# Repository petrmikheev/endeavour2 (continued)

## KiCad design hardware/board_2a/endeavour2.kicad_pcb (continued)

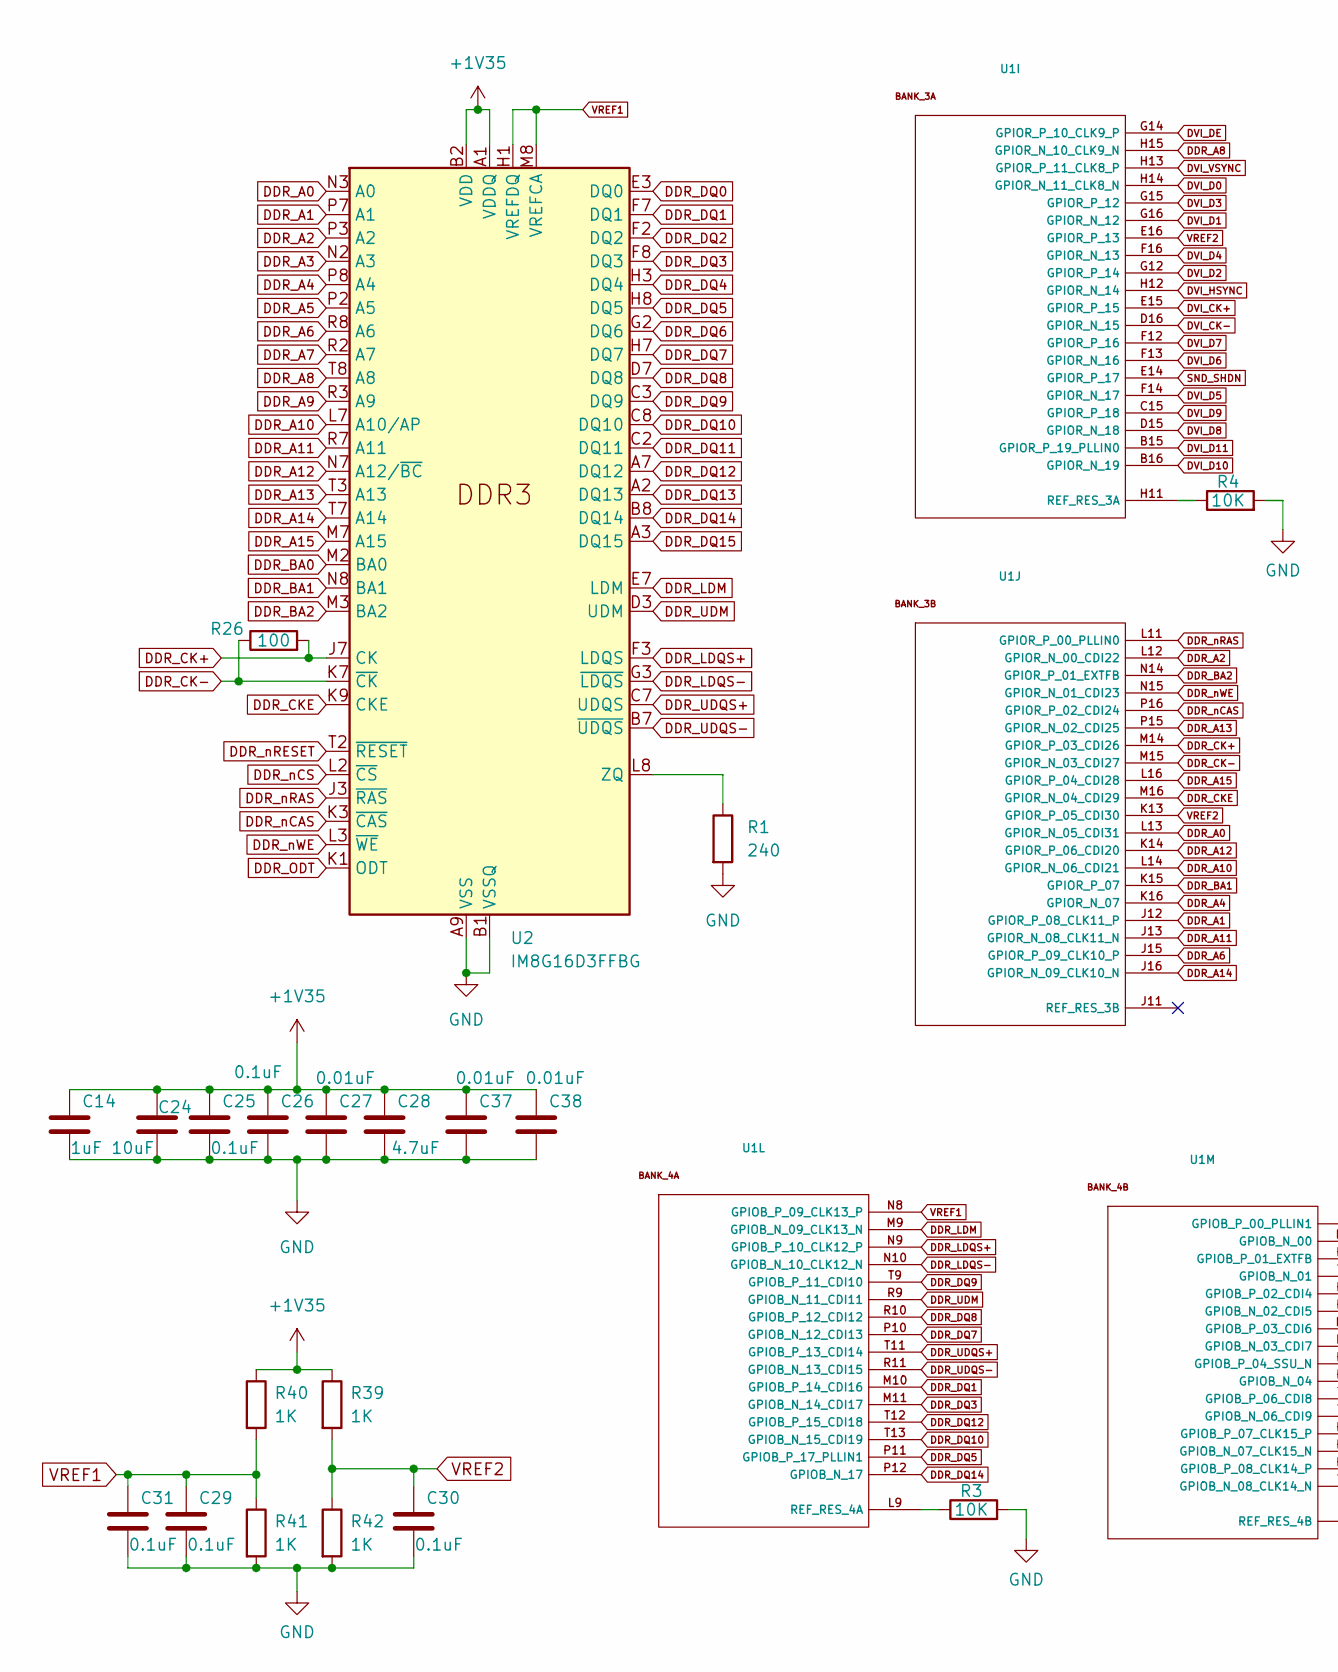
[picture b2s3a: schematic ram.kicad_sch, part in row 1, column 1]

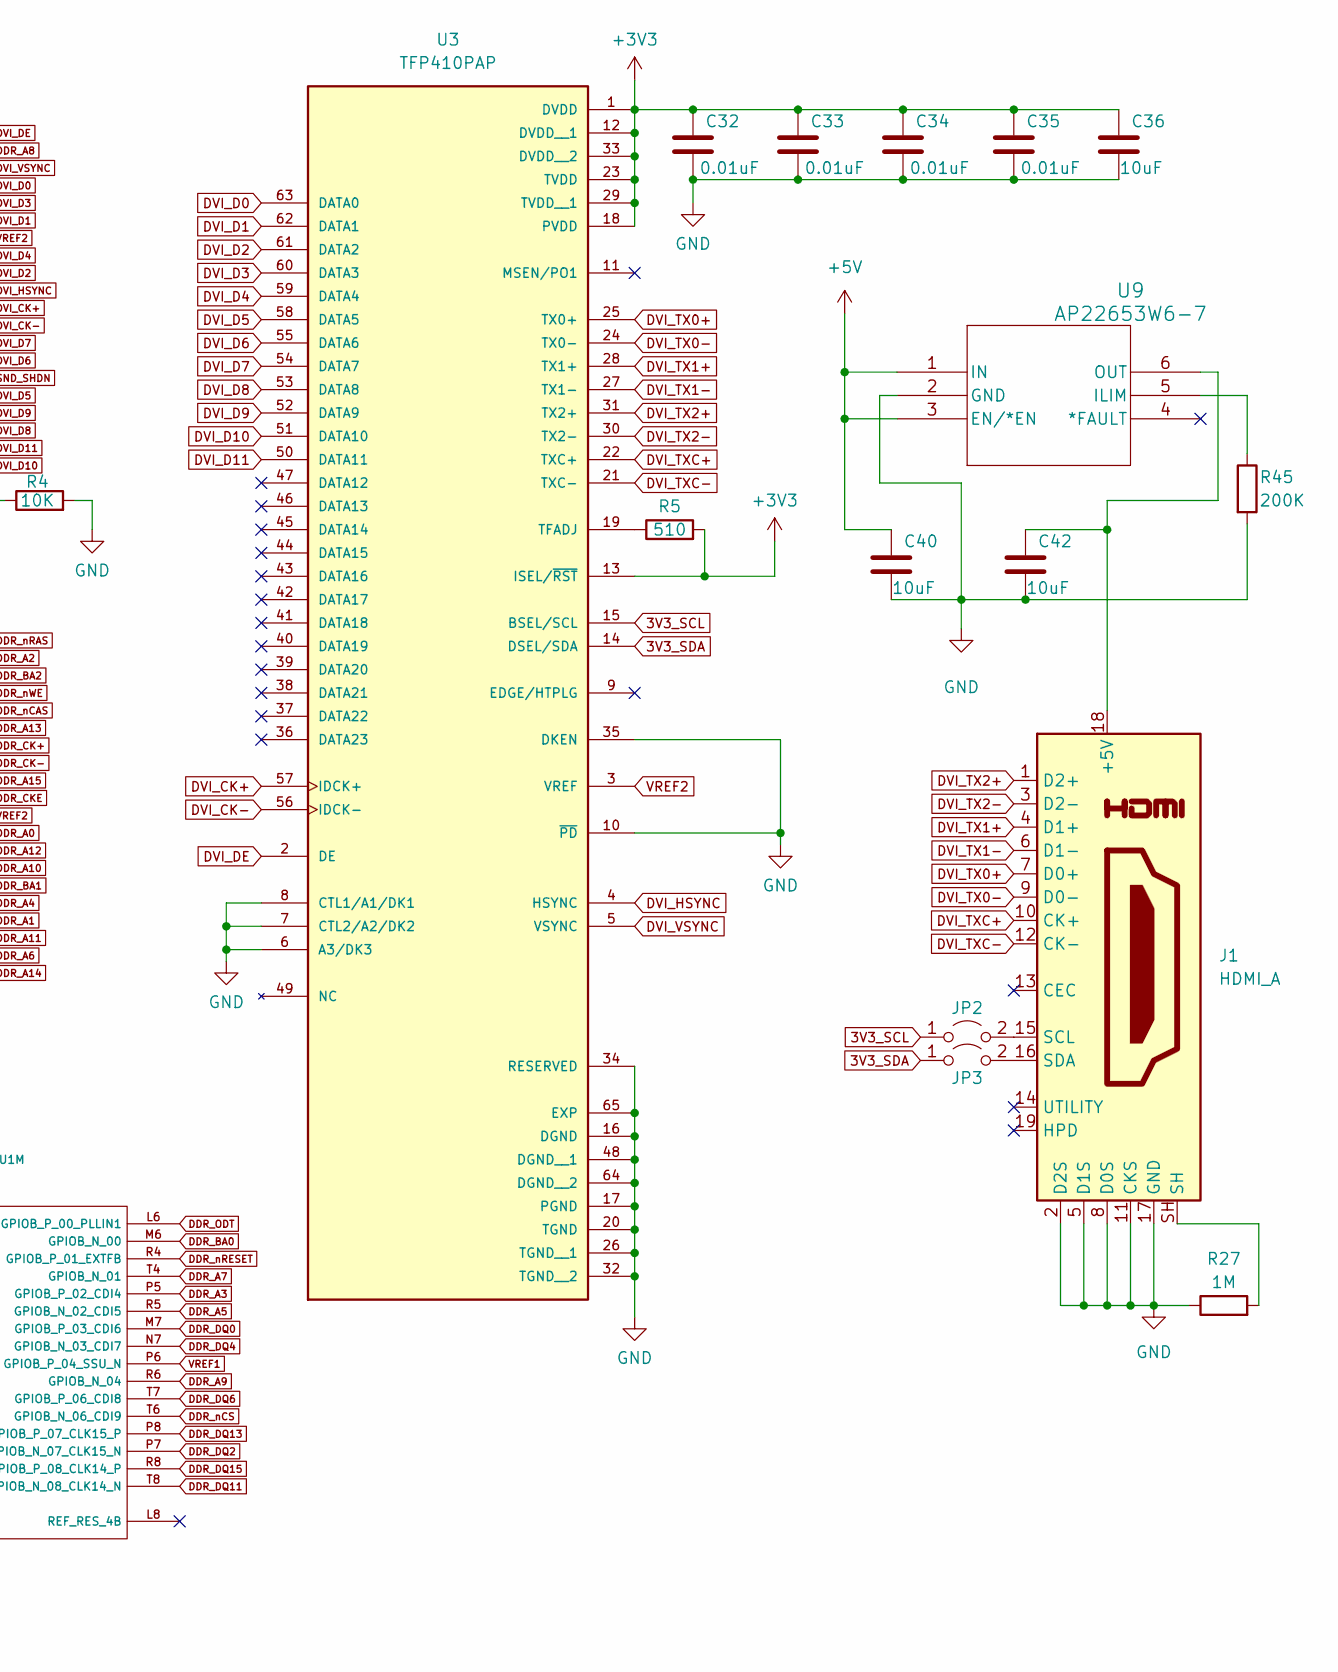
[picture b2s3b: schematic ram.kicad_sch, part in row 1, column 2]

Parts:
C14: 1uF; C_0603_1608Metric
C24, C36, C40, C42: 10uF; C_0603_1608Metric
C25, C26, C29, C30, C31: 0.1uF; C_0603_1608Metric
C27, C32, C33, C34, C35, C37, C38: 0.01uF; C_0603_1608Metric
C28: 4.7uF; C_0603_1608Metric
J1: HDMI_A; HDMI_A_Amphenol_10029449-x01xLF_Horizontal
JP2, JP3: Jumper_2_Bridged; SolderJumper-2_P1.3mm_Open_RoundedPad1.0x1.5mm
R1: 240; R_0603_1608Metric
R3, R4: 10K; R_0603_1608Metric
R5: 510; R_0603_1608Metric
R26: 100; R_0603_1608Metric
R27: 1M; R_0603_1608Metric
R39, R40, R41, R42: 1K; R_0603_1608Metric
R45: 200K; R_0603_1608Metric
U1: Ti60F256; BGA-256_14.0x14.0mm_Layout16x16_P0.8mm_Ball0.45mm_Pad0.32mm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
U2: IM8G16D3FFBG; BGA-96_9.0x13.5mm_Layout2x3x16_P0.8mm
U3: TFP410PAP; IC_TFP410PAP; PARTREV D
U9: AP22653W6-7; SOT26_DIO

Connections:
3V3_SCL: JP2.1 (A), U3.15 (BSEL/SCL); also elsewhere on the board
3V3_SDA: JP3.1 (A), U3.14 (DSEL/SDA); also elsewhere on the board
+1V35: C14.1, C24.1, C25.1, C26.1, C27.1, C28.1, C37.1, C38.1, R39.1, R40.1, U2.A1 (VDDQ), U2.A8 (VDDQ), U2.B2 (VDD), U2.C1 (VDDQ), U2.C9 (VDDQ), U2.D2 (VDDQ), U2.D9 (VDD), U2.E9 (VDDQ), U2.F1 (VDDQ), U2.G7 (VDD), U2.H2 (VDDQ), U2.H9 (VDDQ), U2.K2 (VDD), U2.K8 (VDD), U2.N1 (VDD), U2.N9 (VDD), U2.R1 (VDD), U2.R9 (VDD); also elsewhere on the board
+3V3: C32.1, C33.1, C34.1, C35.1, C36.1, R5.2, U3.1 (DVDD), U3.12 (DVDD__1), U3.13 (ISEL/~RST), U3.18 (PVDD), U3.23 (TVDD), U3.29 (TVDD__1), U3.33 (DVDD__2); also elsewhere on the board
+5V: C40.1, U9.1 (IN), U9.3 (EN/*EN); also elsewhere on the board
DDR_A0: U1.L13 (GPIOR_N_05_CDI31), U2.N3 (A0)
DDR_A1: U1.J12 (GPIOR_P_08_CLK11_P), U2.P7 (A1)
DDR_A2: U1.L12 (GPIOR_N_00_CDI22), U2.P3 (A2)
DDR_A3: U1.P5 (GPIOB_P_02_CDI4), U2.N2 (A3)
DDR_A4: U1.K16 (GPIOR_N_07), U2.P8 (A4)
DDR_A5: U1.R5 (GPIOB_N_02_CDI5), U2.P2 (A5)
DDR_A6: U1.J15 (GPIOR_P_09_CLK10_P), U2.R8 (A6)
DDR_A7: U1.T4 (GPIOB_N_01), U2.R2 (A7)
DDR_A8: U1.H15 (GPIOR_N_10_CLK9_N), U2.T8 (A8)
DDR_A9: U1.R6 (GPIOB_N_04), U2.R3 (A9)
DDR_A10: U1.L14 (GPIOR_N_06_CDI21), U2.L7 (A10/AP)
DDR_A11: U1.J13 (GPIOR_N_08_CLK11_N), U2.R7 (A11)
DDR_A12: U1.K14 (GPIOR_P_06_CDI20), U2.N7 (A12/~BC)
DDR_A13: U1.P15 (GPIOR_N_02_CDI25), U2.T3 (A13)
DDR_A14: U1.J16 (GPIOR_N_09_CLK10_N), U2.T7 (A14)
DDR_A15: U1.L16 (GPIOR_P_04_CDI28), U2.M7 (A15)
DDR_BA0: U1.M6 (GPIOB_N_00), U2.M2 (BA0)
DDR_BA1: U1.K15 (GPIOR_P_07), U2.N8 (BA1)
DDR_BA2: U1.N14 (GPIOR_P_01_EXTFB), U2.M3 (BA2)
DDR_CK+: R26.2, U1.M14 (GPIOR_P_03_CDI26), U2.J7 (CK)
DDR_CK-: R26.1, U1.M15 (GPIOR_N_03_CDI27), U2.K7 (~CK)
DDR_CKE: U1.M16 (GPIOR_N_04_CDI29), U2.K9 (CKE)
DDR_DQ0: U1.M7 (GPIOB_P_03_CDI6), U2.E3 (DQ0)
DDR_DQ1: U1.M10 (GPIOB_P_14_CDI16), U2.F7 (DQ1)
DDR_DQ2: U1.P7 (GPIOB_N_07_CLK15_N), U2.F2 (DQ2)
DDR_DQ3: U1.M11 (GPIOB_N_14_CDI17), U2.F8 (DQ3)
DDR_DQ4: U1.N7 (GPIOB_N_03_CDI7), U2.H3 (DQ4)
DDR_DQ5: U1.P11 (GPIOB_P_17_PLLIN1), U2.H8 (DQ5)
DDR_DQ6: U1.T7 (GPIOB_P_06_CDI8), U2.G2 (DQ6)
DDR_DQ7: U1.P10 (GPIOB_N_12_CDI13), U2.H7 (DQ7)
DDR_DQ8: U1.R10 (GPIOB_P_12_CDI12), U2.D7 (DQ8)
DDR_DQ9: U1.T9 (GPIOB_P_11_CDI10), U2.C3 (DQ9)
DDR_DQ10: U1.T13 (GPIOB_N_15_CDI19), U2.C8 (DQ10)
DDR_DQ11: U1.T8 (GPIOB_N_08_CLK14_N), U2.C2 (DQ11)
DDR_DQ12: U1.T12 (GPIOB_P_15_CDI18), U2.A7 (DQ12)
DDR_DQ13: U1.P8 (GPIOB_P_07_CLK15_P), U2.A2 (DQ13)
DDR_DQ14: U1.P12 (GPIOB_N_17), U2.B8 (DQ14)
DDR_DQ15: U1.R8 (GPIOB_P_08_CLK14_P), U2.A3 (DQ15)
DDR_LDM: U1.M9 (GPIOB_N_09_CLK13_N), U2.E7 (LDM)
DDR_LDQS+: U1.N9 (GPIOB_P_10_CLK12_P), U2.F3 (LDQS)
DDR_LDQS-: U1.N10 (GPIOB_N_10_CLK12_N), U2.G3 (~LDQS)
DDR_ODT: U1.L6 (GPIOB_P_00_PLLIN1), U2.K1 (ODT)
DDR_UDM: U1.R9 (GPIOB_N_11_CDI11), U2.D3 (UDM)
DDR_UDQS+: U1.T11 (GPIOB_P_13_CDI14), U2.C7 (UDQS)
DDR_UDQS-: U1.R11 (GPIOB_N_13_CDI15), U2.B7 (~UDQS)
DDR_nCAS: U1.P16 (GPIOR_P_02_CDI24), U2.K3 (~CAS)
DDR_nCS: U1.T6 (GPIOB_N_06_CDI9), U2.L2 (~CS)
DDR_nRAS: U1.L11 (GPIOR_P_00_PLLIN0), U2.J3 (~RAS)
DDR_nRESET: U1.R4 (GPIOB_P_01_EXTFB), U2.T2 (~RESET)
DDR_nWE: U1.N15 (GPIOR_N_01_CDI23), U2.L3 (~WE)
DVI_CK+: U1.E15 (GPIOR_P_15), U3.57 (IDCK+)
DVI_CK-: U1.D16 (GPIOR_N_15), U3.56 (IDCK-)
DVI_D0: U1.H14 (GPIOR_N_11_CLK8_N), U3.63 (DATA0)
DVI_D1: U1.G16 (GPIOR_N_12), U3.62 (DATA1)
DVI_D2: U1.G12 (GPIOR_P_14), U3.61 (DATA2)
DVI_D3: U1.G15 (GPIOR_P_12), U3.60 (DATA3)
DVI_D4: U1.F16 (GPIOR_N_13), U3.59 (DATA4)
DVI_D5: U1.F14 (GPIOR_N_17), U3.58 (DATA5)
DVI_D6: U1.F13 (GPIOR_N_16), U3.55 (DATA6)
DVI_D7: U1.F12 (GPIOR_P_16), U3.54 (DATA7)
DVI_D8: U1.D15 (GPIOR_N_18), U3.53 (DATA8)
DVI_D9: U1.C15 (GPIOR_P_18), U3.52 (DATA9)
DVI_D10: U1.B16 (GPIOR_N_19), U3.51 (DATA10)
DVI_D11: U1.B15 (GPIOR_P_19_PLLIN0), U3.50 (DATA11)
DVI_DE: U1.G14 (GPIOR_P_10_CLK9_P), U3.2 (DE)
DVI_HSYNC: U1.H12 (GPIOR_N_14), U3.4 (HSYNC)
DVI_TX0+: J1.7 (D0+), U3.25 (TX0+)
DVI_TX0-: J1.9 (D0-), U3.24 (TX0-)
DVI_TX1+: J1.4 (D1+), U3.28 (TX1+)
DVI_TX1-: J1.6 (D1-), U3.27 (TX1-)
DVI_TX2+: J1.1 (D2+), U3.31 (TX2+)
DVI_TX2-: J1.3 (D2-), U3.30 (TX2-)
DVI_TXC+: J1.10 (CK+), U3.22 (TXC+)
DVI_TXC-: J1.12 (CK-), U3.21 (TXC-)
DVI_VSYNC: U1.H13 (GPIOR_P_11_CLK8_P), U3.5 (VSYNC)
GND: C14.2, C24.2, C25.2, C26.2, C27.2, C28.2, C29.2, C30.2, C31.2, C32.2, C33.2, C34.2, C35.2, C36.2, C37.2, C38.2, C40.2, C42.2, J1.2 (D2S), J1.5 (D1S), J1.8 (D0S), J1.11 (CKS), J1.17 (GND), R1.2, R3.2, R4.2, R27.1, R41.2, R42.2, R45.2, U2.A9 (VSS), U2.B1 (VSSQ), U2.B3 (VSS), U2.B9 (VSSQ), U2.D1 (VSSQ), U2.D8 (VSSQ), U2.E1 (VSS), U2.E2 (VSSQ), U2.E8 (VSSQ), U2.F9 (VSSQ), U2.G1 (VSSQ), U2.G8 (VSS), U2.G9 (VSSQ), U2.J2 (VSS), U2.J8 (VSS), U2.M1 (VSS), U2.M9 (VSS), U2.P1 (VSS), U2.P9 (VSS), U2.T1 (VSS), U2.T9 (VSS), U3.6 (A3/DK3), U3.7 (CTL2/A2/DK2), U3.8 (CTL1/A1/DK1), U3.10 (~PD), U3.16 (DGND), U3.17 (PGND), U3.20 (TGND), U3.26 (TGND__1), U3.32 (TGND__2), U3.34 (RESERVED), U3.35 (DKEN), U3.48 (DGND__1), U3.64 (DGND__2), U3.65 (EXP), U9.2 (GND); also elsewhere on the board
unnamed: C42.1, J1.18 (+5V), U9.6 (OUT)
unnamed: J1.SH, R27.2
unnamed: J1.15 (SCL), JP2.2 (B)
unnamed: J1.16 (SDA), JP3.2 (B)
unnamed: R4.1, U1.H11 (REF_RES_3A)
unnamed: R3.1, U1.L9 (REF_RES_4A)
unnamed: R1.1, U2.L8 (ZQ)
unnamed: R5.1, U3.19 (TFADJ)
unnamed: R45.1, U9.5 (ILIM)
SND_SHDN: U1.E14 (GPIOR_P_17); also elsewhere on the board
VREF1: C29.1, C31.1, R40.2, R41.1, U1.N8 (GPIOB_P_09_CLK13_P), U1.P6 (GPIOB_P_04_SSU_N), U2.H1 (VREFDQ), U2.M8 (VREFCA)
VREF2: C30.1, R39.2, R42.1, U1.E16 (GPIOR_P_13), U1.K13 (GPIOR_P_05_CDI30), U3.3 (VREF)

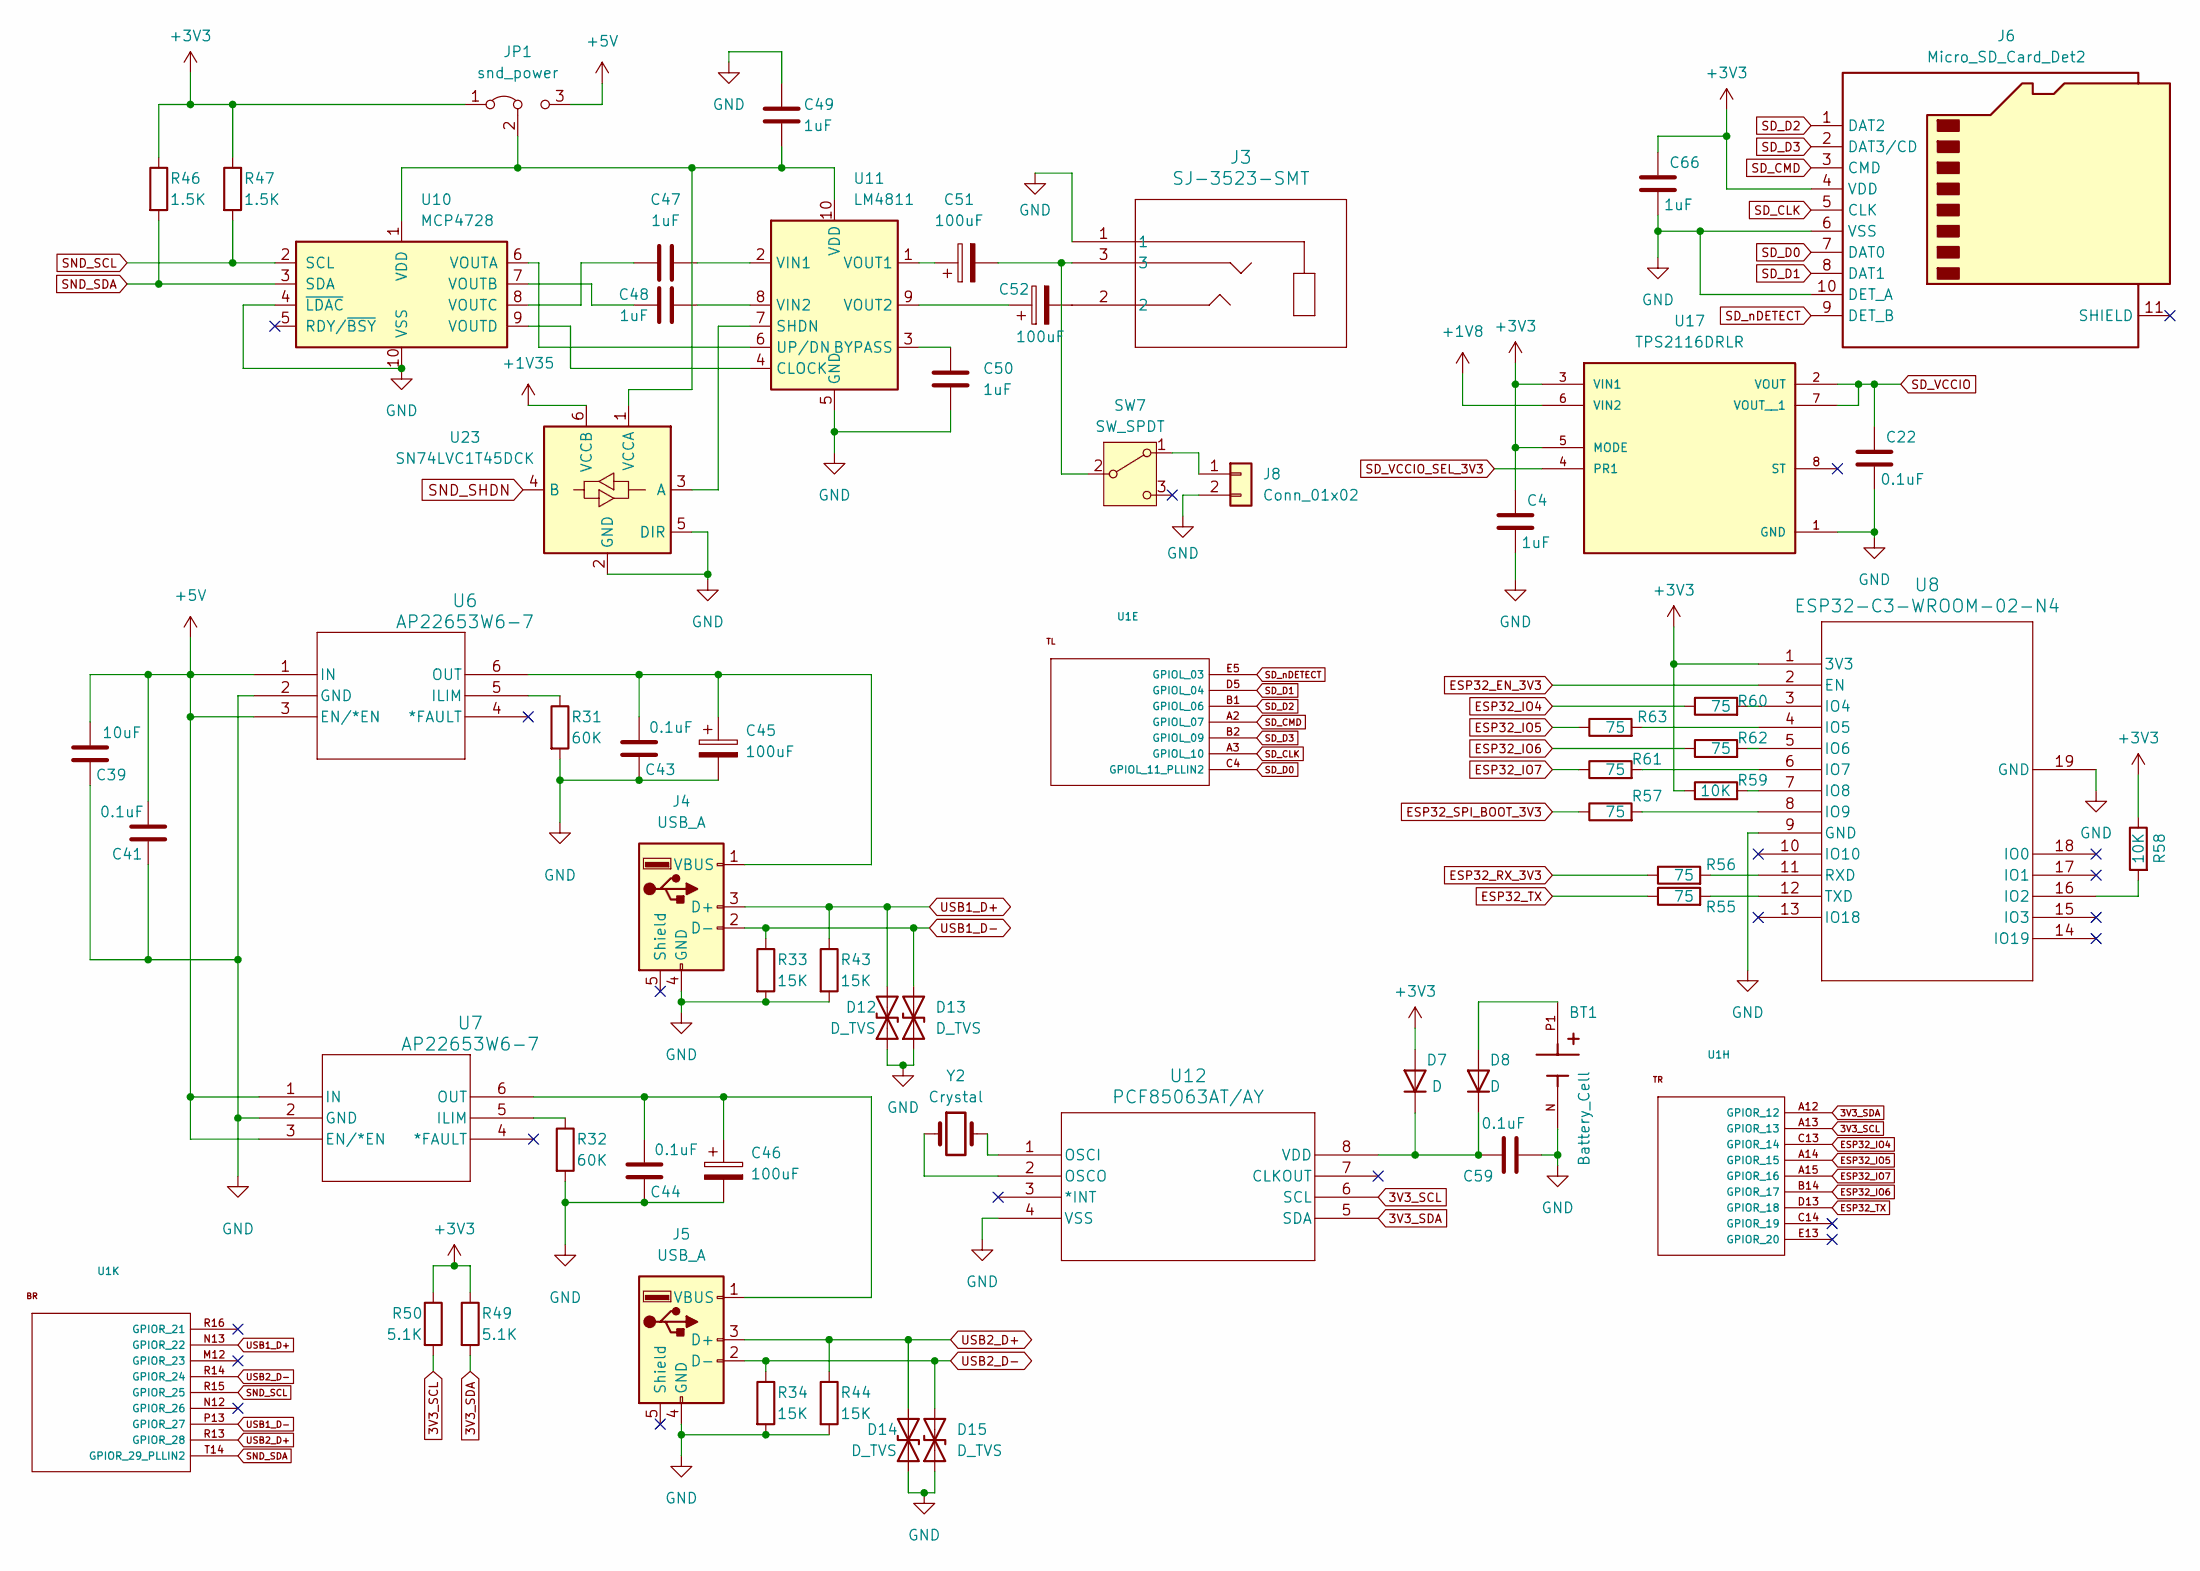
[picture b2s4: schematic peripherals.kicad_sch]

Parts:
BT1: Battery_Cell; BAT_2989; PARTREV A
C4, C47, C48, C49, C50, C66: 1uF; C_0603_1608Metric
C22, C41, C43, C44, C59: 0.1uF; C_0603_1608Metric
C39: 10uF; C_0603_1608Metric
C45, C46: 100uF; CP_EIA-3528-12_Kemet-T
C51, C52: 100uF; CP_Elec_5x5.3
D7, D8: D; D_SOD-323
D12, D13, D14, D15: D_TVS; D_0603_1608Metric
J3: SJ-3523-SMT; SJ-3523-SMT_CUD
J4, J5: USB_A; USB_A_Receptacle_GCT_USB1046
J6: Micro_SD_Card_Det2; microSD_HC_Molex_104031-0811
J8: Conn_01x02; PinHeader_1x02_P2.54mm_Vertical
JP1: snd_power; SolderJumper-3_P1.3mm_Open_Pad1.0x1.5mm
R31, R32: 60K; R_0603_1608Metric
R33, R34, R43, R44: 15K; R_0603_1608Metric
R46, R47: 1.5K; R_0603_1608Metric
R49, R50: 5.1K; R_0603_1608Metric
R55, R56, R57, R60, R61, R62, R63: 75; R_0603_1608Metric
R58, R59: 10K; R_0603_1608Metric
SW7: SW_SPDT; SW_Slide_SPDT_Angled_CK_OS102011MA1Q
U1: Ti60F256; BGA-256_14.0x14.0mm_Layout16x16_P0.8mm_Ball0.45mm_Pad0.32mm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
U6, U7: AP22653W6-7; SOT26_DIO
U8: ESP32-C3-WROOM-02-N4; ESP32-C3-WROOM-02
U10: MCP4728; MSOP-10_3x3mm_P0.5mm
U11: LM4811; TSSOP-10_3x3mm_P0.5mm
U12: PCF85063AT/AY; SOIC-8_3.9x4.9mm_P1.27mm
U17: TPS2116DRLR; SOTFL50P160X60-8N; PARTREV A
U23: SN74LVC1T45DCK; SOT-363_SC-70-6
Y2: Crystal; Crystal_SMD_MicroCrystal_CC7V-T1A-2Pin_3.2x1.5mm_HandSolder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

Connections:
3V3_SCL: R50.2, U1.A13 (GPIOR_13), U12.6 (SCL); also elsewhere on the board
3V3_SDA: R49.2, U1.A12 (GPIOR_12), U12.5 (SDA); also elsewhere on the board
+1V8: U17.6 (VIN2); also elsewhere on the board
+1V35: U23.6 (VCCB); also elsewhere on the board
+3V3: C4.1, C66.1, D7.2 (A), J6.4 (VDD), JP1.1 (A), R46.1, R47.1, R49.1, R50.1, R58.1, R59.1, U8.1 (3V3), U17.3 (VIN1), U17.5 (MODE); also elsewhere on the board
+5V: C39.2, C41.2, JP1.3 (B), U6.1 (IN), U6.3 (EN/*EN), U7.1 (IN), U7.3 (EN/*EN); also elsewhere on the board
ESP32_EN_3V3: U8.2 (EN); also elsewhere on the board
ESP32_IO4: R60.1, U1.C13 (GPIOR_14)
ESP32_IO5: R63.1, U1.A14 (GPIOR_15)
ESP32_IO6: R62.1, U1.B14 (GPIOR_17)
ESP32_IO7: R61.1, U1.A15 (GPIOR_16)
ESP32_RX_3V3: R56.1; also elsewhere on the board
ESP32_SPI_BOOT_3V3: R57.1; also elsewhere on the board
ESP32_TX: R55.1, U1.D13 (GPIOR_18)
GND: BT1.N, C4.2, C22.2, C39.1, C41.1, C43.1, C44.1, C45.2, C46.2, C49.1, C50.2, C59.2, C66.2, D12.1 (A1), D13.1 (A1), D14.1 (A1), D15.1 (A1), J3.1, J4.4 (GND), J5.4 (GND), J6.6 (VSS), J6.10 (DET_A), J8.2, R31.2, R32.2, R33.2, R34.2, R43.2, R44.2, U6.2 (GND), U7.2 (GND), U8.9 (GND), U8.19 (GND), U10.4 (~LDAC), U10.10 (VSS), U11.5 (GND), U12.4 (VSS), U17.1 (GND), U23.2 (GND), U23.5 (DIR); also elsewhere on the board
unnamed: C52.2, J3.2
unnamed: C59.1, D7.1 (K), D8.1 (K), U12.8 (VDD)
unnamed: BT1.P1, D8.2 (A)
unnamed: C43.2, C45.1, J4.1 (VBUS), U6.6 (OUT)
unnamed: C44.2, C46.1, J5.1 (VBUS), U7.6 (OUT)
unnamed: J8.1, SW7.1 (A)
unnamed: C49.2, JP1.2 (C), U10.1 (VDD), U11.10 (VDD), U23.1 (VCCA)
unnamed: C51.2, J3.3, SW7.2 (B)
unnamed: R31.1, U6.5 (ILIM)
unnamed: R32.1, U7.5 (ILIM)
unnamed: R58.2, U8.16 (IO2)
unnamed: R60.2, U8.3 (IO4)
unnamed: R63.2, U8.4 (IO5)
unnamed: R62.2, U8.5 (IO6)
unnamed: R61.2, U8.6 (IO7)
unnamed: R59.2, U8.7 (IO8)
unnamed: R57.2, U8.8 (IO9)
unnamed: R56.2, U8.11 (RXD)
unnamed: R55.2, U8.12 (TXD)
unnamed: U10.6 (VOUTA), U11.6 (UP/DN)
unnamed: C48.1, U10.7 (VOUTB)
unnamed: C47.1, U10.8 (VOUTC)
unnamed: U10.9 (VOUTD), U11.4 (CLOCK)
unnamed: C50.1, U11.3 (BYPASS)
unnamed: U11.7 (SHDN), U23.3 (A)
unnamed: C47.2, U11.2 (VIN1)
unnamed: C48.2, U11.8 (VIN2)
unnamed: C51.1, U11.1 (VOUT1)
unnamed: C52.1, U11.9 (VOUT2)
unnamed: U12.1 (OSCI), Y2.2
unnamed: U12.2 (OSCO), Y2.1
SD_CLK: J6.5 (CLK), U1.A3 (GPIOL_10)
SD_CMD: J6.3 (CMD), U1.A2 (GPIOL_07)
SD_D0: J6.7 (DAT0), U1.C4 (GPIOL_11_PLLIN2)
SD_D1: J6.8 (DAT1), U1.D5 (GPIOL_04)
SD_D2: J6.1 (DAT2), U1.B1 (GPIOL_06)
SD_D3: J6.2 (DAT3/CD), U1.B2 (GPIOL_09)
SD_VCCIO: C22.1, U17.2 (VOUT), U17.7 (VOUT__1); also elsewhere on the board
SD_VCCIO_SEL_3V3: U17.4 (PR1); also elsewhere on the board
SD_nDETECT: J6.9 (DET_B), U1.E5 (GPIOL_03)
SND_SCL: R47.2, U1.R15 (GPIOR_25), U10.2 (SCL)
SND_SDA: R46.2, U1.T14 (GPIOR_29_PLLIN2), U10.3 (SDA)
SND_SHDN: U23.4 (B); also elsewhere on the board
USB1_D+: D12.2 (A2), J4.3 (D+), R43.1, U1.N13 (GPIOR_22)
USB1_D-: D13.2 (A2), J4.2 (D-), R33.1, U1.P13 (GPIOR_27)
USB2_D+: D14.2 (A2), J5.3 (D+), R44.1, U1.R13 (GPIOR_28)
USB2_D-: D15.2 (A2), J5.2 (D-), R34.1, U1.R14 (GPIOR_24)

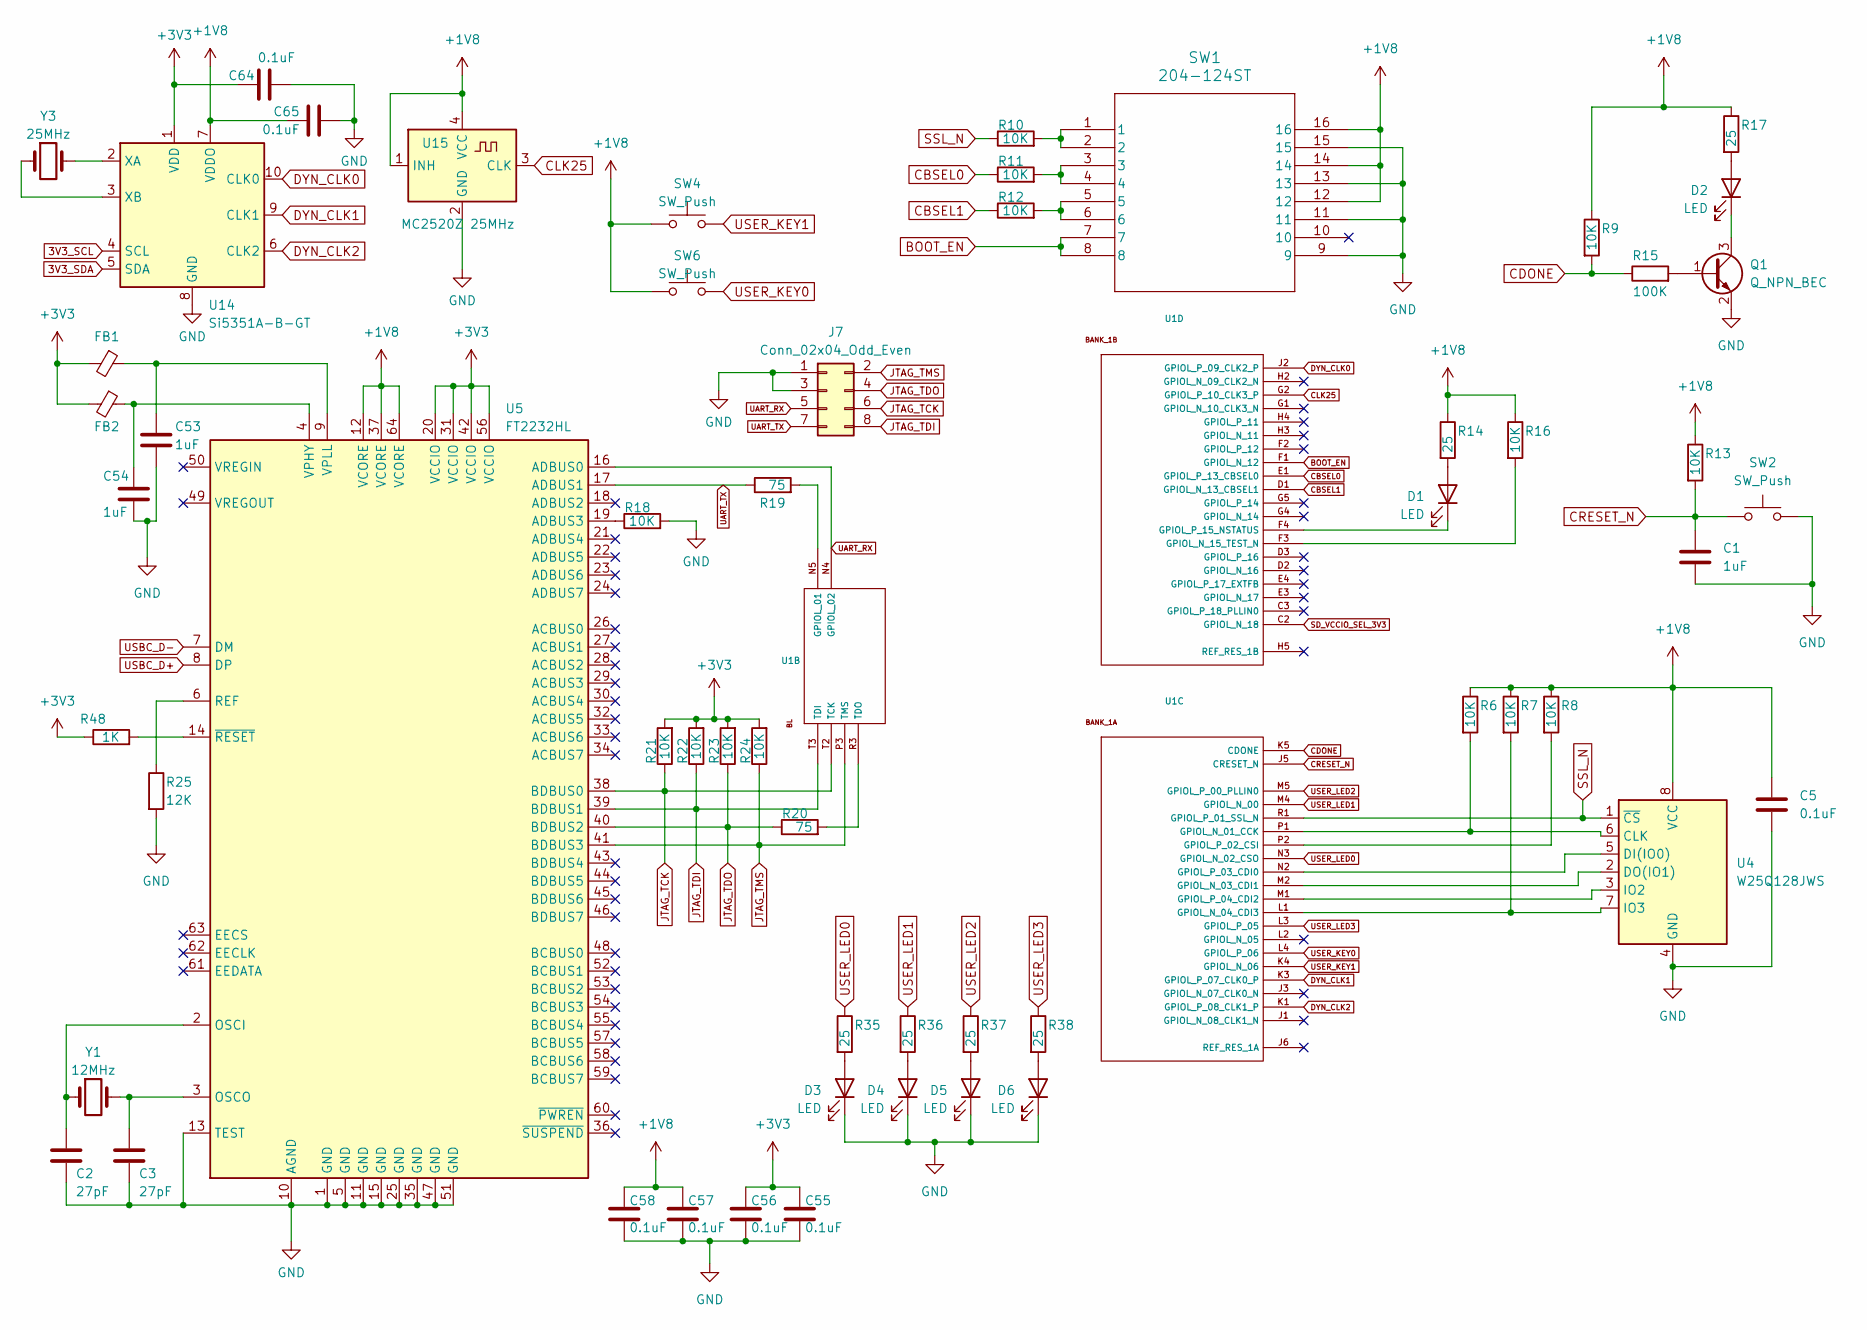
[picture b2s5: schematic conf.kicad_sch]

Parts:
C1, C53, C54: 1uF; C_0603_1608Metric
C2, C3: 27pF; C_0603_1608Metric
C5, C55, C56, C57, C58, C64, C65: 0.1uF; C_0603_1608Metric
D1, D2, D3, D4, D5, D6: LED; LED_0603_1608Metric
FB1, FB2: L_0603_1608Metric
J7: Conn_02x04_Odd_Even; PinHeader_2x04_P2.54mm_Vertical
Q1: Q_NPN_BEC; SC-59
R6, R7, R8, R9, R10, R11, R12, R13, R16, R18, R21, R22, R23, R24: 10K; R_0603_1608Metric
R14, R17, R35, R36, R37, R38: 25; R_0603_1608Metric
R15: 100K; R_0603_1608Metric
R19, R20: 75; R_0603_1608Metric
R25: 12K; R_0603_1608Metric
R48: 1K; R_0603_1608Metric
SW1: 204-124ST; SPDT_204-124_CTS
SW2, SW4, SW6: SW_Push; SW_PUSH_6mm
U1: Ti60F256; BGA-256_14.0x14.0mm_Layout16x16_P0.8mm_Ball0.45mm_Pad0.32mm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
U4: W25Q128JWS; SOIC-8_5.23x5.23mm_P1.27mm
U5: FT2232HL; LQFP-64_10x10mm_P0.5mm
U14: Si5351A-B-GT; MSOP-10_3x3mm_P0.5mm
U15: MC2520Z 25MHz; Oscillator_SMD_Kyocera_KC2520Z-4Pin_2.5x2.0mm
Y1: 12MHz; XTAL_ECS-120-20-3X-TR
Y3: 25MHz; XTAL_ECS-120-20-3X-TR

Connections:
3V3_SCL: U14.4 (SCL); also elsewhere on the board
3V3_SDA: U14.5 (SDA); also elsewhere on the board
+1V8: C5.1, C57.1, C58.1, C65.1, R6.1, R7.1, R8.1, R9.1, R13.1, R14.1, R16.1, R17.1, SW1.12, SW1.14, SW1.16, SW4.1, SW6.1, U4.8 (VCC), U5.12 (VCORE), U5.37 (VCORE), U5.64 (VCORE), U14.7 (VDDO), U15.1 (INH), U15.4 (VCC); also elsewhere on the board
+3V3: C55.1, C56.1, C64.1, FB1.2, FB2.2, R21.2, R22.2, R23.2, R24.2, R48.1, U5.20 (VCCIO), U5.31 (VCCIO), U5.42 (VCCIO), U5.56 (VCCIO), U14.1 (VDD); also elsewhere on the board
BOOT_EN: SW1.7, SW1.8, U1.F1 (GPIOL_N_12)
CBSEL0: R11.1, U1.E1 (GPIOL_P_13_CBSEL0)
CBSEL1: R12.1, U1.D1 (GPIOL_N_13_CBSEL1)
CDONE: R9.2, R15.1, U1.K5 (CDONE)
CLK25: U1.G2 (GPIOL_P_10_CLK3_P), U15.3 (CLK)
CRESET_N: C1.1, R13.2, SW2.1, U1.J5 (CRESET_N); also elsewhere on the board
DYN_CLK0: U1.J2 (GPIOL_P_09_CLK2_P), U14.10 (CLK0)
DYN_CLK1: U1.K3 (GPIOL_P_07_CLK0_P), U14.9 (CLK1)
DYN_CLK2: U1.K1 (GPIOL_P_08_CLK1_P), U14.6 (CLK2)
GND: C1.2, C2.2, C3.2, C5.2, C53.2, C54.2, C55.2, C56.2, C57.2, C58.2, C64.2, C65.2, D3.1 (K), D4.1 (K), D5.1 (K), D6.1 (K), J7.1, J7.3, Q1.2 (E), R18.2, R25.2, SW1.9, SW1.11, SW1.13, SW1.15, SW2.2, U4.4 (GND), U5.1 (GND), U5.5 (GND), U5.10 (AGND), U5.11 (GND), U5.13 (TEST), U5.15 (GND), U5.25 (GND), U5.35 (GND), U5.47 (GND), U5.51 (GND), U14.8 (GND), U15.2 (GND); also elsewhere on the board
JTAG_TCK: J7.6, R21.1, U1.T2 (TCK), U5.38 (BDBUS0)
JTAG_TDI: J7.8, R22.1, U1.T3 (TDI), U5.39 (BDBUS1)
JTAG_TDO: J7.4, R20.1, R23.1, U5.40 (BDBUS2)
JTAG_TMS: J7.2, R24.1, U1.P3 (TMS), U5.41 (BDBUS3)
unnamed: D1.2 (A), R14.2
unnamed: D1.1 (K), U1.F4 (GPIOL_P_15_NSTATUS)
unnamed: D2.2 (A), R17.2
unnamed: D2.1 (K), Q1.3 (C)
unnamed: D3.2 (A), R35.2
unnamed: D4.2 (A), R36.2
unnamed: D5.2 (A), R37.2
unnamed: D6.2 (A), R38.2
unnamed: Q1.1 (B), R15.2
unnamed: R10.2, SW1.1, SW1.2
unnamed: R11.2, SW1.3, SW1.4
unnamed: R12.2, SW1.5, SW1.6
unnamed: R19.2, U1.N5 (GPIOL_01)
unnamed: R20.2, U1.R3 (TDO)
unnamed: R6.2, U1.P1 (GPIOL_N_01_CCK), U4.6 (CLK)
unnamed: U1.M2 (GPIOL_N_03_CDI1), U4.2 (DO(IO1))
unnamed: R7.2, U1.L1 (GPIOL_N_04_CDI3), U4.7 (IO3)
unnamed: R8.2, U1.P2 (GPIOL_P_02_CSI)
unnamed: U1.N2 (GPIOL_P_03_CDI0), U4.5 (DI(IO0))
unnamed: U1.M1 (GPIOL_P_04_CDI2), U4.3 (IO2)
unnamed: R16.2, U1.F3 (GPIOL_N_15_TEST_N)
unnamed: R18.1, U5.19 (ADBUS3)
unnamed: C2.1, U5.2 (OSCI), Y1.1
unnamed: C3.1, U5.3 (OSCO), Y1.2
unnamed: R25.1, U5.6 (REF)
unnamed: C54.1, FB2.1, U5.4 (VPHY)
unnamed: C53.1, FB1.1, U5.9 (VPLL)
unnamed: R48.2, U5.14 (~RESET)
unnamed: U14.2 (XA), Y3.2
unnamed: U14.3 (XB), Y3.1
SD_VCCIO_SEL_3V3: U1.C2 (GPIOL_N_18); also elsewhere on the board
SSL_N: R10.1, U1.R1 (GPIOL_P_01_SSL_N), U4.1 (~CS)
UART_RX: J7.5, U1.N4 (GPIOL_02), U5.16 (ADBUS0)
UART_TX: J7.7, R19.1, U5.17 (ADBUS1)
USBC_D+: U5.8 (DP); also elsewhere on the board
USBC_D-: U5.7 (DM); also elsewhere on the board
USER_KEY0: SW6.2, U1.L4 (GPIOL_P_06)
USER_KEY1: SW4.2, U1.K4 (GPIOL_N_06)
USER_LED0: R35.1, U1.N3 (GPIOL_N_02_CSO)
USER_LED1: R36.1, U1.M4 (GPIOL_N_00)
USER_LED2: R37.1, U1.M5 (GPIOL_P_00_PLLIN0)
USER_LED3: R38.1, U1.L3 (GPIOL_P_05)
